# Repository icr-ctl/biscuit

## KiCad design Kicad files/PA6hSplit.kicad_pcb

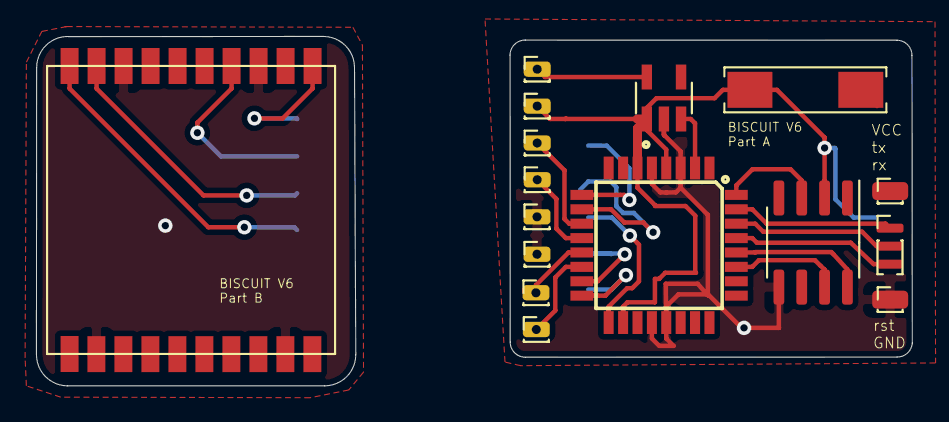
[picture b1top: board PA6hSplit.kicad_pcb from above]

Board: 2 copper layers, 48.7 x 19.4 mm, 5 parts (1 on the bottom side), 14 nets.

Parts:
U1: ATMEGA328P_TQFP; TQFP32-08
U2: DS3231MZ; SOIC-8_3.9x4.9mm_P1.27mm
U3: RFM95W-915S2; HOPERF_RFM9XW_SMD
U4: MIC5225-3.3YM5-TR; SOT95P280X145-5N
U5: PA6H; Pa6h

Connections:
A4: U1.27, U2.7
A5: U1.28, U2.8
D2: U1.32, U2.3
D4: U1.2, U4.3
D5: U1.9, U3.6
D6: U1.10, U3.5
D7: U1.11, U5.9
D8: U1.12, U5.10
GND: U1.3, U1.5, U1.20, U1.21, U2.5, U3.1, U3.8, U3.10, U4.2, U5.3, U5.8, U5.12, U5.19
GPSPOW: U4.5, U5.1
MISO: U1.16, U3.2
MOSI: U1.15, U3.3
SCK: U1.17, U3.4
VCC: U1.4, U1.6, U1.18, U2.2, U3.13, U4.1, U5.4
